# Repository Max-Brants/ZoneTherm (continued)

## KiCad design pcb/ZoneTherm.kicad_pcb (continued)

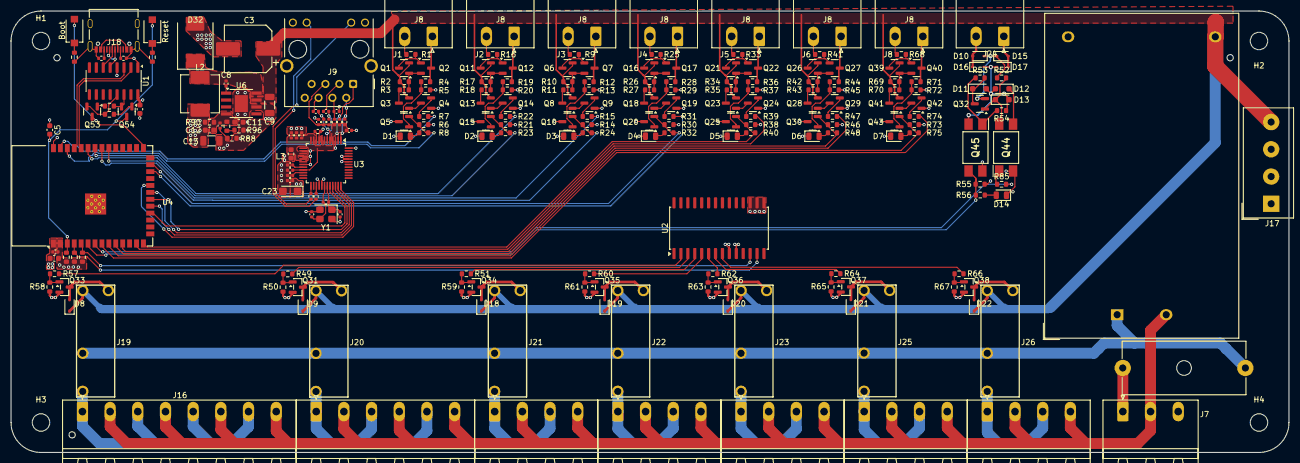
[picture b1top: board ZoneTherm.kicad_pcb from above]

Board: 4 copper layers, 234.5 x 81.0 mm, 236 parts (0 on the bottom side), 161 nets.

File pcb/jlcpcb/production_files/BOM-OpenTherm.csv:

Comment,Designator,Footprint,LCSC,Quantity
0.01uf,C8,C_0402_1005Metric,C15195,1
0.1uf,"C18,C19,C20,C21,C22",C_0402_1005Metric,C141382,5
0.1uf,C6,C_0603_1608Metric,C14663,1
0.1uf,C10,C_0402_1005Metric,C1525,1
0.1uf,C1,C_0402_1005Metric,C307331,1
1.5k,R55,R_0603_1608Metric,C22843,1
100,"R10,R17,R2,R26,R34,R42,R54,R69",R_0603_1608Metric,C22775,8
100uf,C13,C_1206_3216Metric,C15008,1
10K,"R90,R91,R92,R95",R_0603_1608Metric,C25804,4
10R,R122,R_0402_1005Metric,C25077,1
10k,"R13,R20,R29,R37,R45,R5,R50,R58,R59,R61,R63,R65,R67,R72,R93,R94",R_0603_1608Metric,C25804,16
10nf,"C15,C17,C24",C_0402_1005Metric,C15195,3
10uf/16v,C23,CP_EIA-3216-18_Kemet-A,C7171,1
12.4K,R125,R_0402_1005Metric,C11692,1
1500pf,C12,C_0603_1608Metric,C1595,1
150pf,C11,C_0603_1608Metric,C1594,1
15uh/3A,L2,L_Changjiang_FXL0630,C5189959,1
18pf,"C26,C27",C_0402_1005Metric,C1549,2
1M,R126,R_0402_1005Metric,C26083,1
1N4148WS,"D10,D15,D16,D17,D18,D19,D20,D21,D22,D8,D9",D_SOD-323,C2128,11
1k,"R14,R21,R30,R38,R46,R49,R51,R56,R57,R6,R60,R62,R64,R66,R73",R_0603_1608Metric,C21190,15
1uf,C5,C_0603_1608Metric,C15849,1
20k,"R12,R19,R28,R36,R4,R44,R71",R_0603_1608Metric,C4184,7
220,R53,R_0603_1608Metric,C22962,1
22nf,C16,C_0402_1005Metric,C1532,1
22uf,C2,C_0603_1608Metric,C59461,1
25MH,Y1,Crystal_SMD_TXC_7M-4Pin_3.2x2.5mm,C9006,1
2K,R96,R_0603_1608Metric,C22975,1
3.9K,R89,R_0603_1608Metric,C23018,1
33,"R11,R18,R27,R3,R35,R43,R70",R_0603_1608Metric,C23140,7
330,"R52,R85",R_0603_1608Metric,C23138,2
330,"R123,R124",R_0402_1005Metric,C25104,2
33k,"R1,R16,R25,R33,R41,R68,R9",R_0603_1608Metric,C4216,7
4.7uf,C25,C_0402_1005Metric,C23733,1
4.7uf,C9,C_1206_3216Metric,C29823,1
49R9,"R118,R119,R120,R121",R_0402_1005Metric,C25120,4
4k7,"R15,R22,R31,R39,R47,R7,R74,R83,R84",R_0603_1608Metric,C23162,9
5.1K,"R86,R87",R_0402_1005Metric,C25905,2
51,"R23,R24,R32,R40,R48,R75,R8",R_0603_1608Metric,C23197,7
549,R88,R_0603_1608Metric,C23204,1
6.8nF,"C14,C7",C_0402_1005Metric,C1542,2
BC848C,"Q10,Q14,Q15,Q19,Q20,Q24,Q25,Q29,Q30,Q31,Q33,Q34,Q35,Q36,Q37,Q38,Q4,Q42,Q43,Q5,Q53,Q54,Q9",SOT-23,C2146,23
BC858B,"Q1,Q11,Q12,Q13,Q16,Q17,Q18,Q2,Q21,Q22,Q23,Q26,Q27,Q28,Q3,Q32,Q39,Q40,Q41,Q6,Q7,Q8",SOT-23,C8542,22
BLM18PG121SN1D,L3,L_0603_1608Metric,C14709,1
Boot,SW1,SW-SMD_L3.9-W3.0-P4.45,C720477,1
CH340C,U1,SOIC-16_3.9x9.9mm_P1.27mm,C84681,1
G5NB-1A-E-24VDC,"J19,J20,J21,J22,J23,J25,J26",RELAY-TH_G5NB-1A-E-24VDC,C34758,7
LED,"D1,D14,D2,D3,D4,D5,D6,D7",LED_0805_2012Metric,C2297,8
MRBS340,D32,D_SMC,C16237,1
RJ45_Hanrun_HR911105A_Horizontal,J9,RJ45_Hanrun_HR911105A_Horizontal,C12074,1
Reset,SW2,SW-SMD_L3.9-W3.0-P4.45,C720477,1
TPS5430DDA,U6,TI_SO-PowerPAD-8,C9864,1
USB_C_Receptacle,J18,USB_C_Receptacle_Palconn_UTC16-G,C2765186,1
W5500,U3,LQFP-48_7x7mm_P0.5mm,C32843,1
Conn_01x02,J5,"PhoenixContact_MSTBA_2,5_2-G-5,08_1x02_P5.08mm_Horizontal",,1
Conn_01x02,J2,"PhoenixContact_MSTBA_2,5_2-G-5,08_1x02_P5.08mm_Horizontal",,1
Fuse,F1,Fuseholder_Cylinder-5x20mm_Schurter_0031_8201_Horizontal_Open,,1
Conn_01x02,J8,"PhoenixContact_MSTBA_2,5_2-G-5,08_1x02_P5.08mm_Horizontal",,1
Screw_Terminal,J17,Altech_AK100_1x04_P5.00mm,,1
4V3,D12,D_SOD-323_HandSoldering,,1
Conn_01x04,J11,"PhoenixContact_MSTBA_2,5_4-G-5,08_1x04_P5.08mm_Horizontal",,1
13V,D13,D_SOD-323_HandSoldering,,1
ESP32-S3-WROOM-1,U4,ESP32-S3-WROOM-1,,1
Conn_01x06,J10,"PhoenixContact_MSTBA_2,5_6-G-5,08_1x06_P5.08mm_Horizontal",,1
4V7,D11,D_SOD-323_HandSoldering,,1
PC817XNNIP1B,Q45,SOP254P960X420-4N,,1
Conn_01x02,J4,"PhoenixContact_MSTBA_2,5_2-G-5,08_1x02_P5.08mm_Horizontal",,1
Conn_01x04,J13,"PhoenixContact_MSTBA_2,5_4-G-5,08_1x04_P5.08mm_Horizontal",,1
MCP23017_SO,U2,SOIC-28W_7.5x17.9mm_P1.27mm,,1
Conn_01x02,J3,"PhoenixContact_MSTBA_2,5_2-G-5,08_1x02_P5.08mm_Horizontal",,1
Conn_01x04,J12,"PhoenixContact_MSTBA_2,5_4-G-5,08_1x04_P5.08mm_Horizontal",,1
Conn_01x02,J24,"PhoenixContact_MSTBA_2,5_2-G-5,08_1x02_P5.08mm_Horizontal",,1
Conn_01x04,J14,"PhoenixContact_MSTBA_2,5_4-G-5,08_1x04_P5.08mm_Horizontal",,1
Conn_01x02,J6,"PhoenixContact_MSTBA_2,5_2-G-5,08_1x02_P5.08mm_Horizontal",,1
Conn_01x04,J15,"PhoenixContact_MSTBA_2,5_4-G-5,08_1x04_P5.08mm_Horizontal",,1
PC817XNNIP1B,Q44,SOP254P960X420-4N,,1
Conn_01x03,J7,"PhoenixContact_MSTBA_2,5_3-G-5,08_1x03_P5.08mm_Horizontal",,1
Conn_01x02,J1,"PhoenixContact_MSTBA_2,5_2-G-5,08_1x02_P5.08mm_Horizontal",,1
Conn_01x08,J16,"PhoenixContact_MSTBA_2,5_8-G-5,08_1x08_P5.08mm_Horizontal",,1
330 uf,C3,CP_Elec_8x10.5,,1
